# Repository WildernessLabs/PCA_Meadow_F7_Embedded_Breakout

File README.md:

# PCA_Meadow_F7_Embedded_Breakout
Printed Circuit Assembly (PCA) design of the breakout dev board for the Meadow F7 Embedded SMT Module

Designed using Kicad 5.1.6 

Import the fp-lib-table (found in the Circuit_Part_Libraries depot) to make sure your libraries work
WP_LIB is where your "Circuit_Part_Libraries\Libraried_Kicad" is located. 

Gerbers, drills and stack up are located in PCB_FAB folder
BOM is located in Assembly Folder
Pick and Place files are located in the Assembly folder

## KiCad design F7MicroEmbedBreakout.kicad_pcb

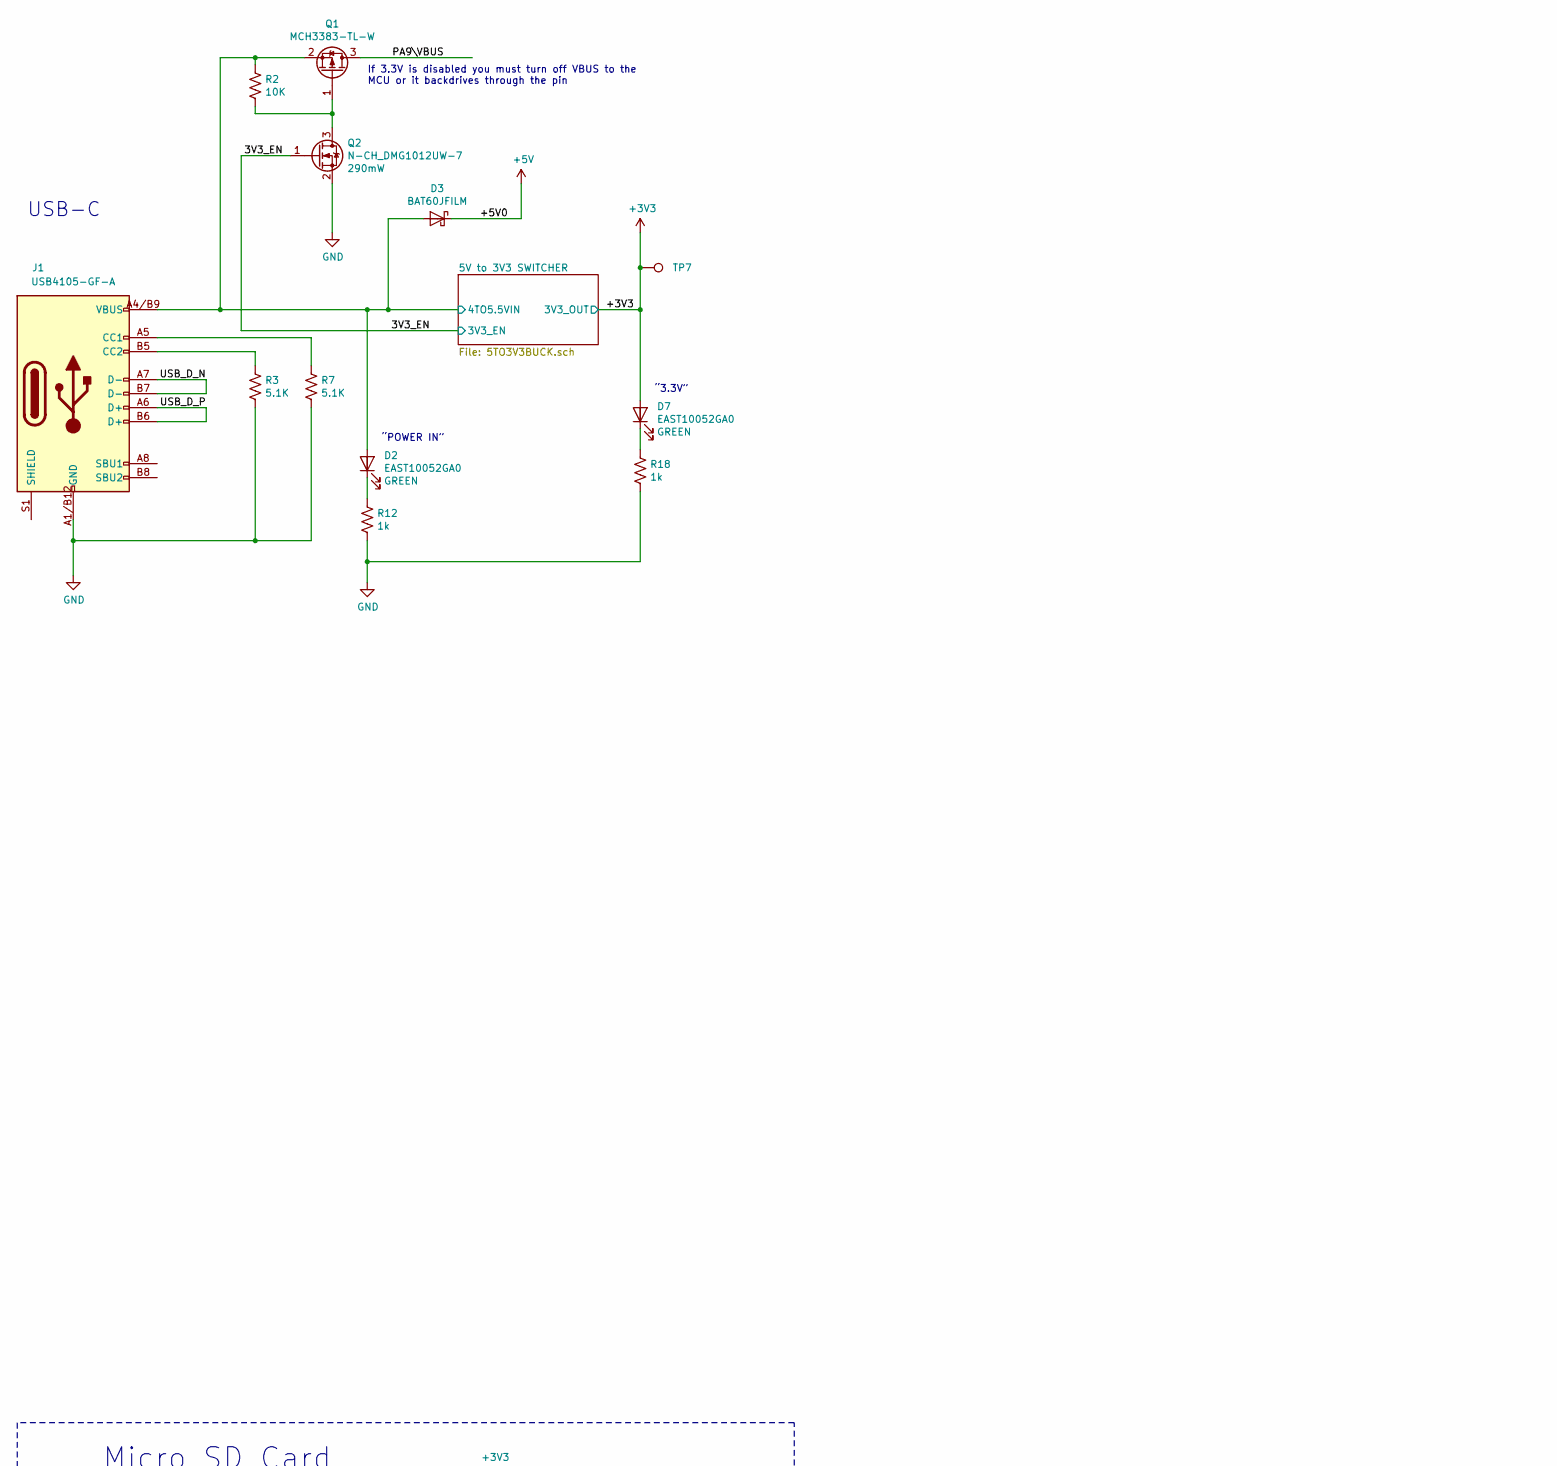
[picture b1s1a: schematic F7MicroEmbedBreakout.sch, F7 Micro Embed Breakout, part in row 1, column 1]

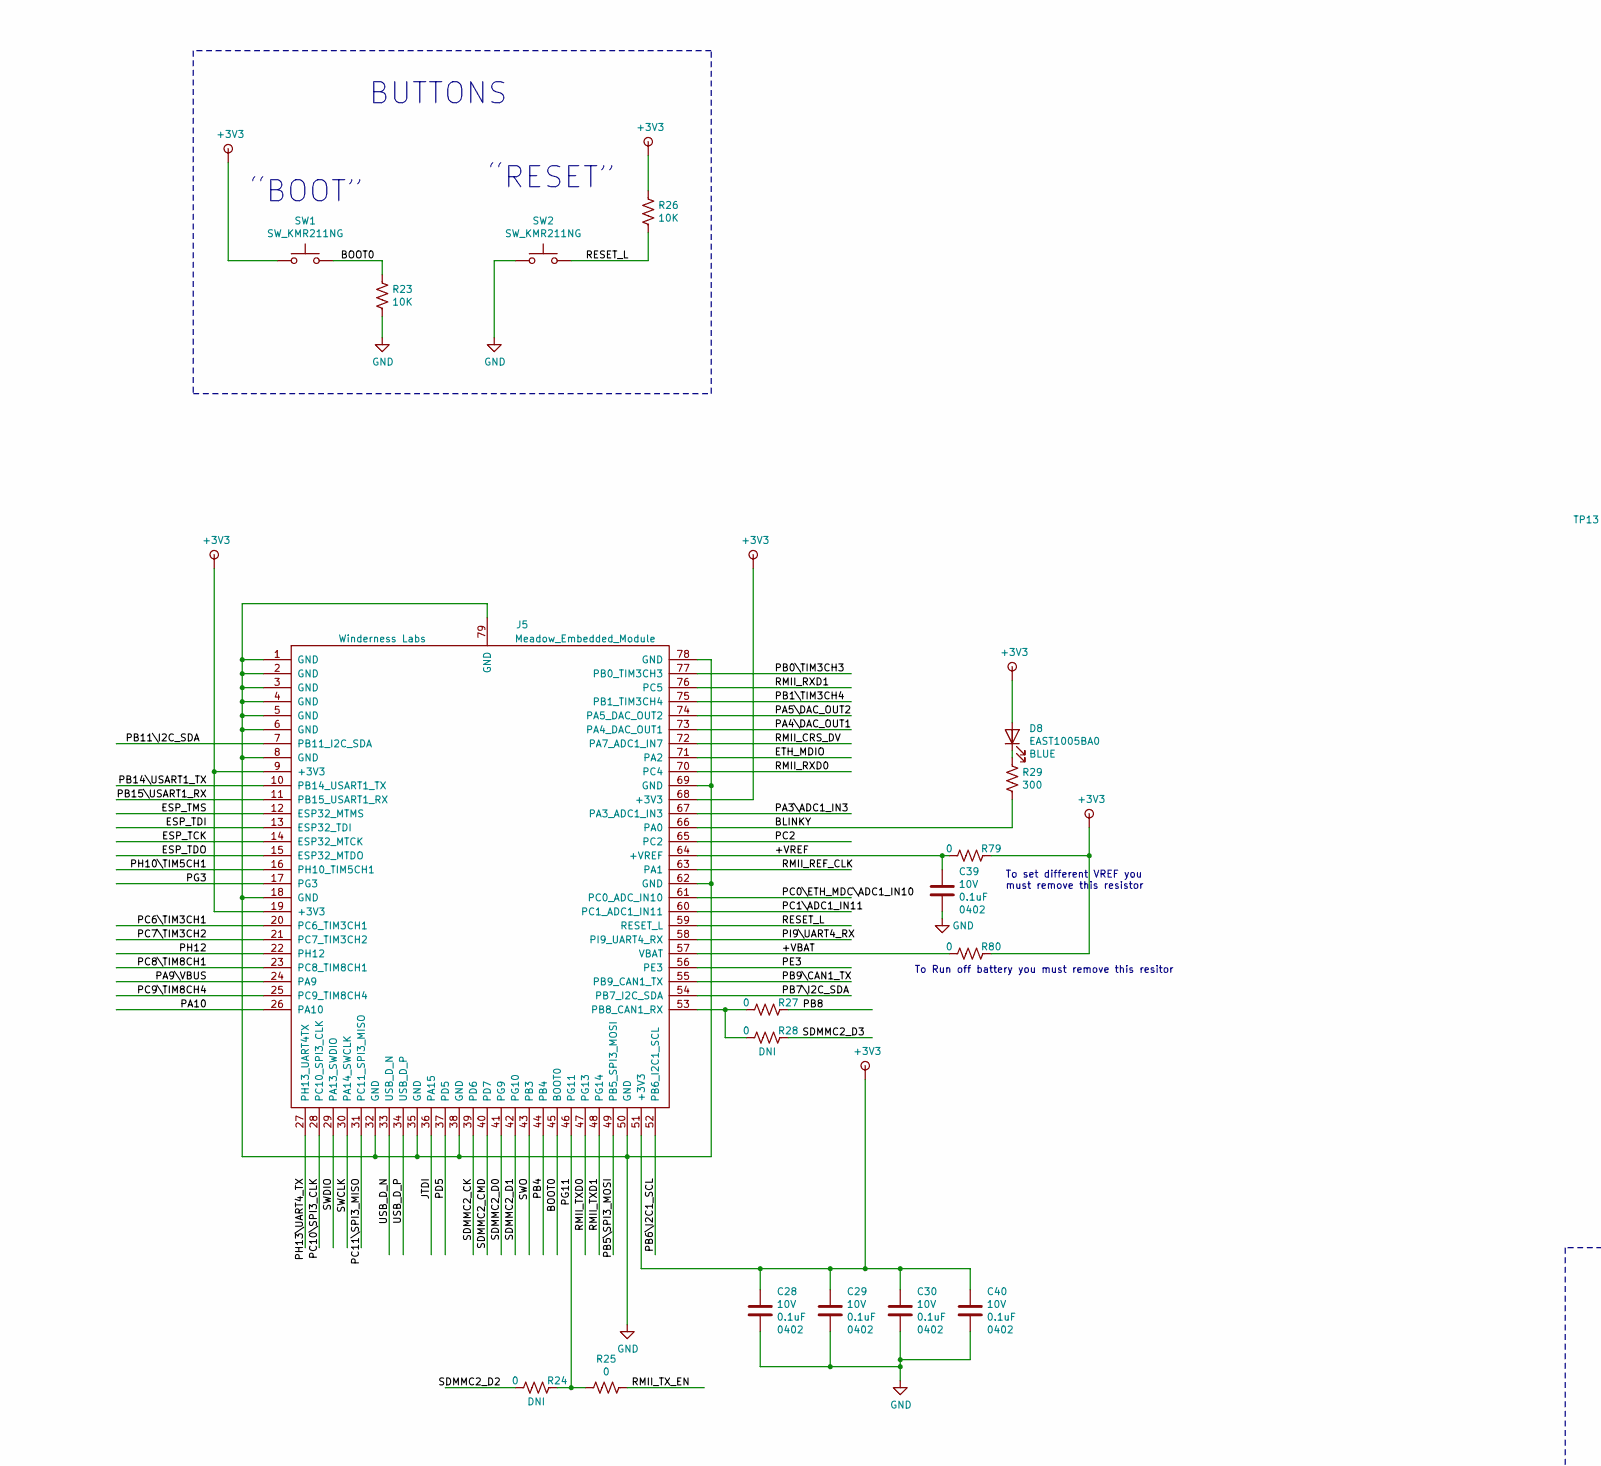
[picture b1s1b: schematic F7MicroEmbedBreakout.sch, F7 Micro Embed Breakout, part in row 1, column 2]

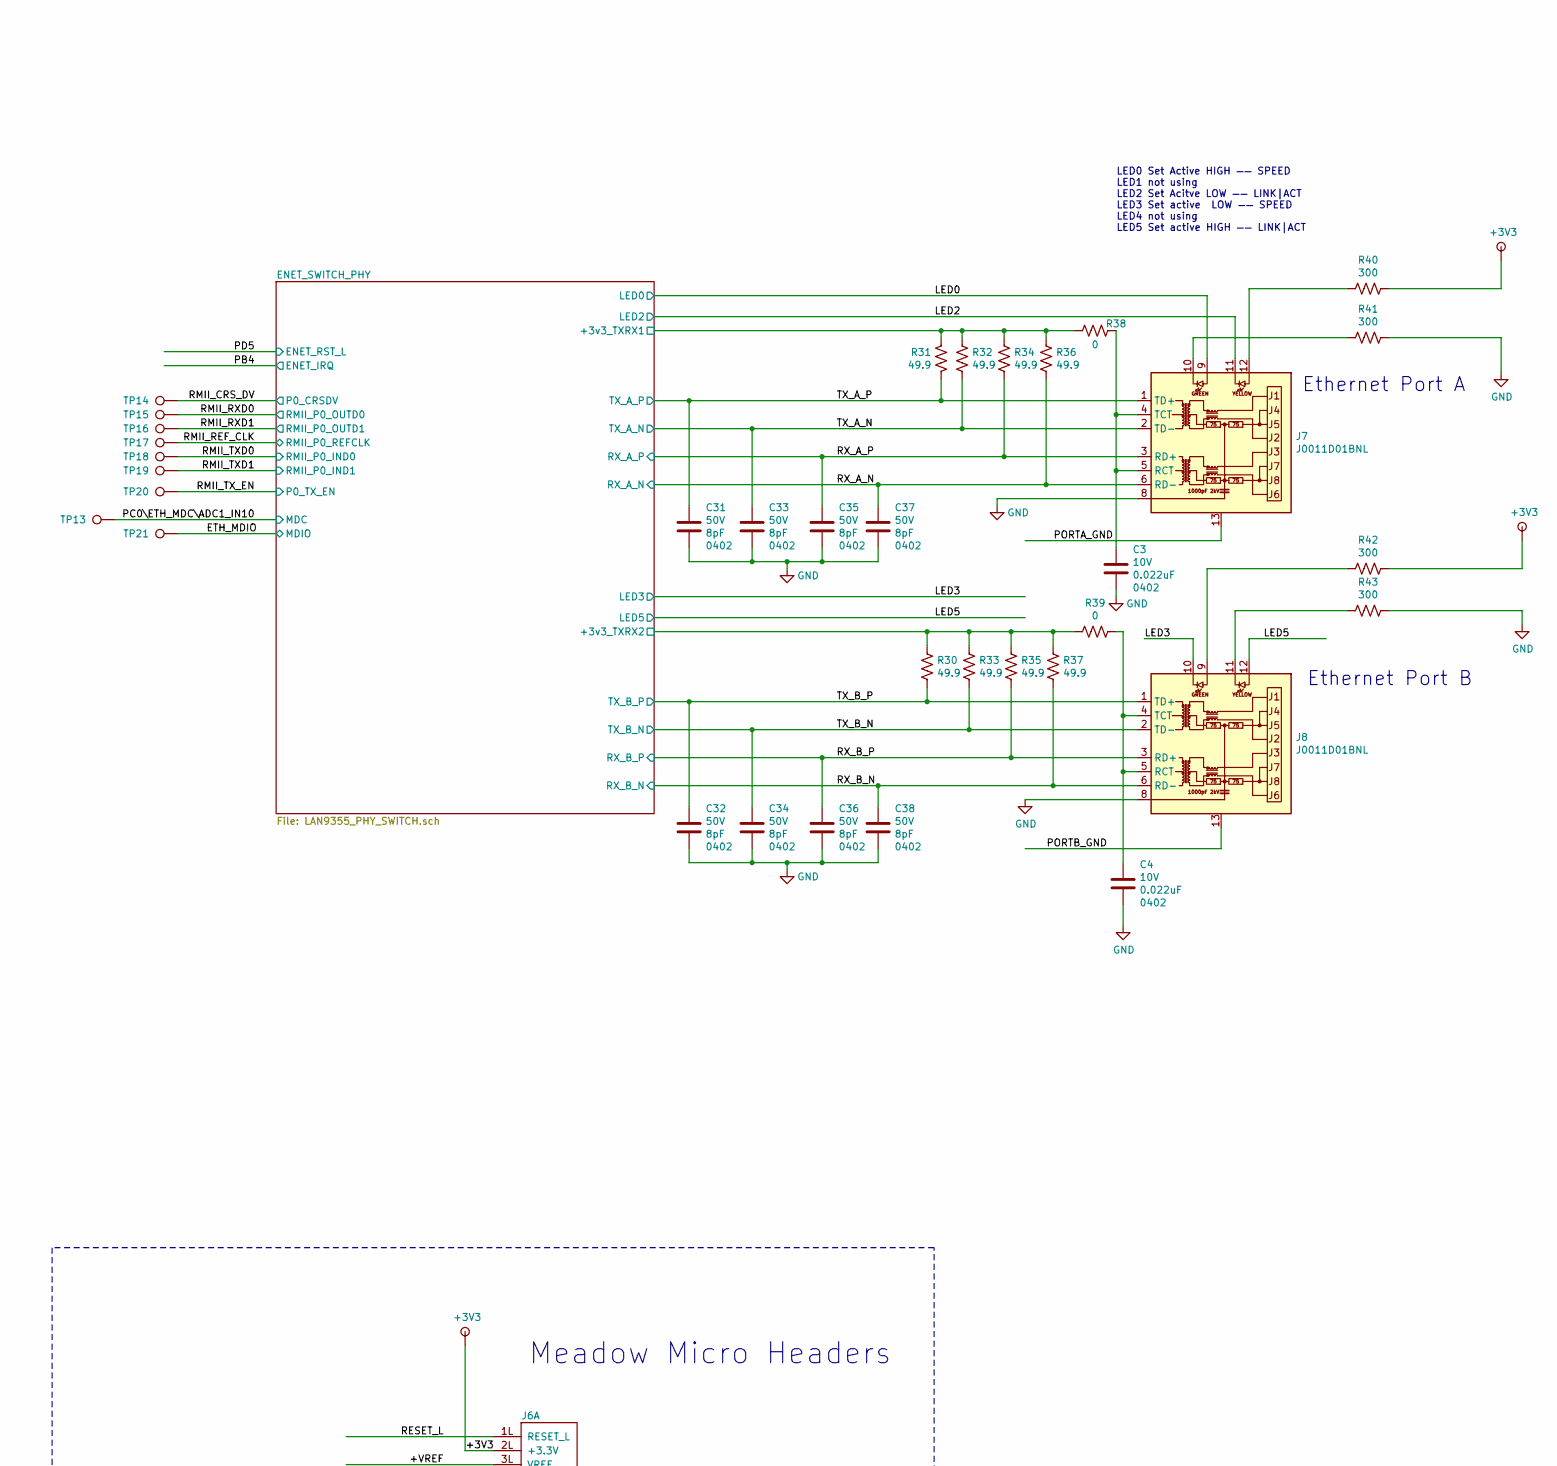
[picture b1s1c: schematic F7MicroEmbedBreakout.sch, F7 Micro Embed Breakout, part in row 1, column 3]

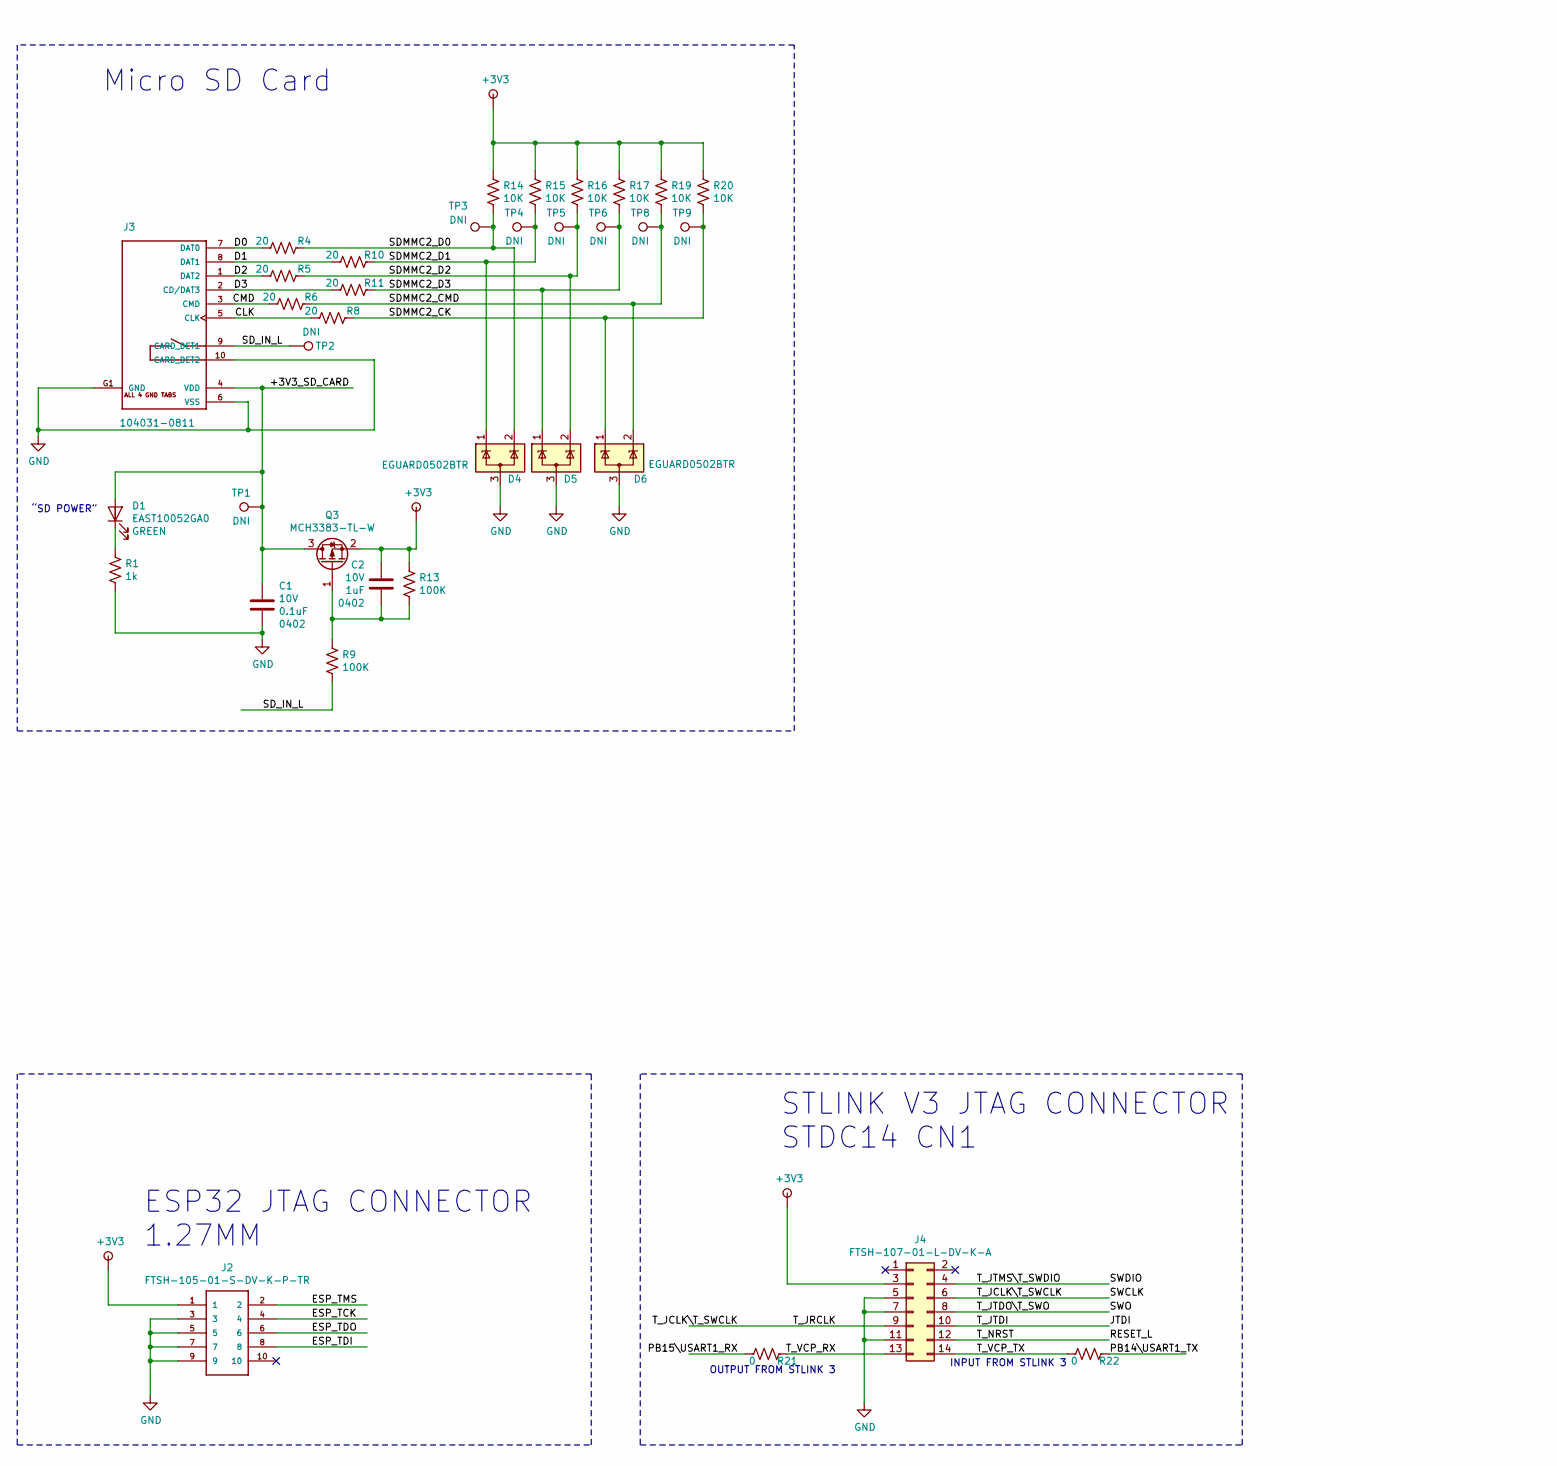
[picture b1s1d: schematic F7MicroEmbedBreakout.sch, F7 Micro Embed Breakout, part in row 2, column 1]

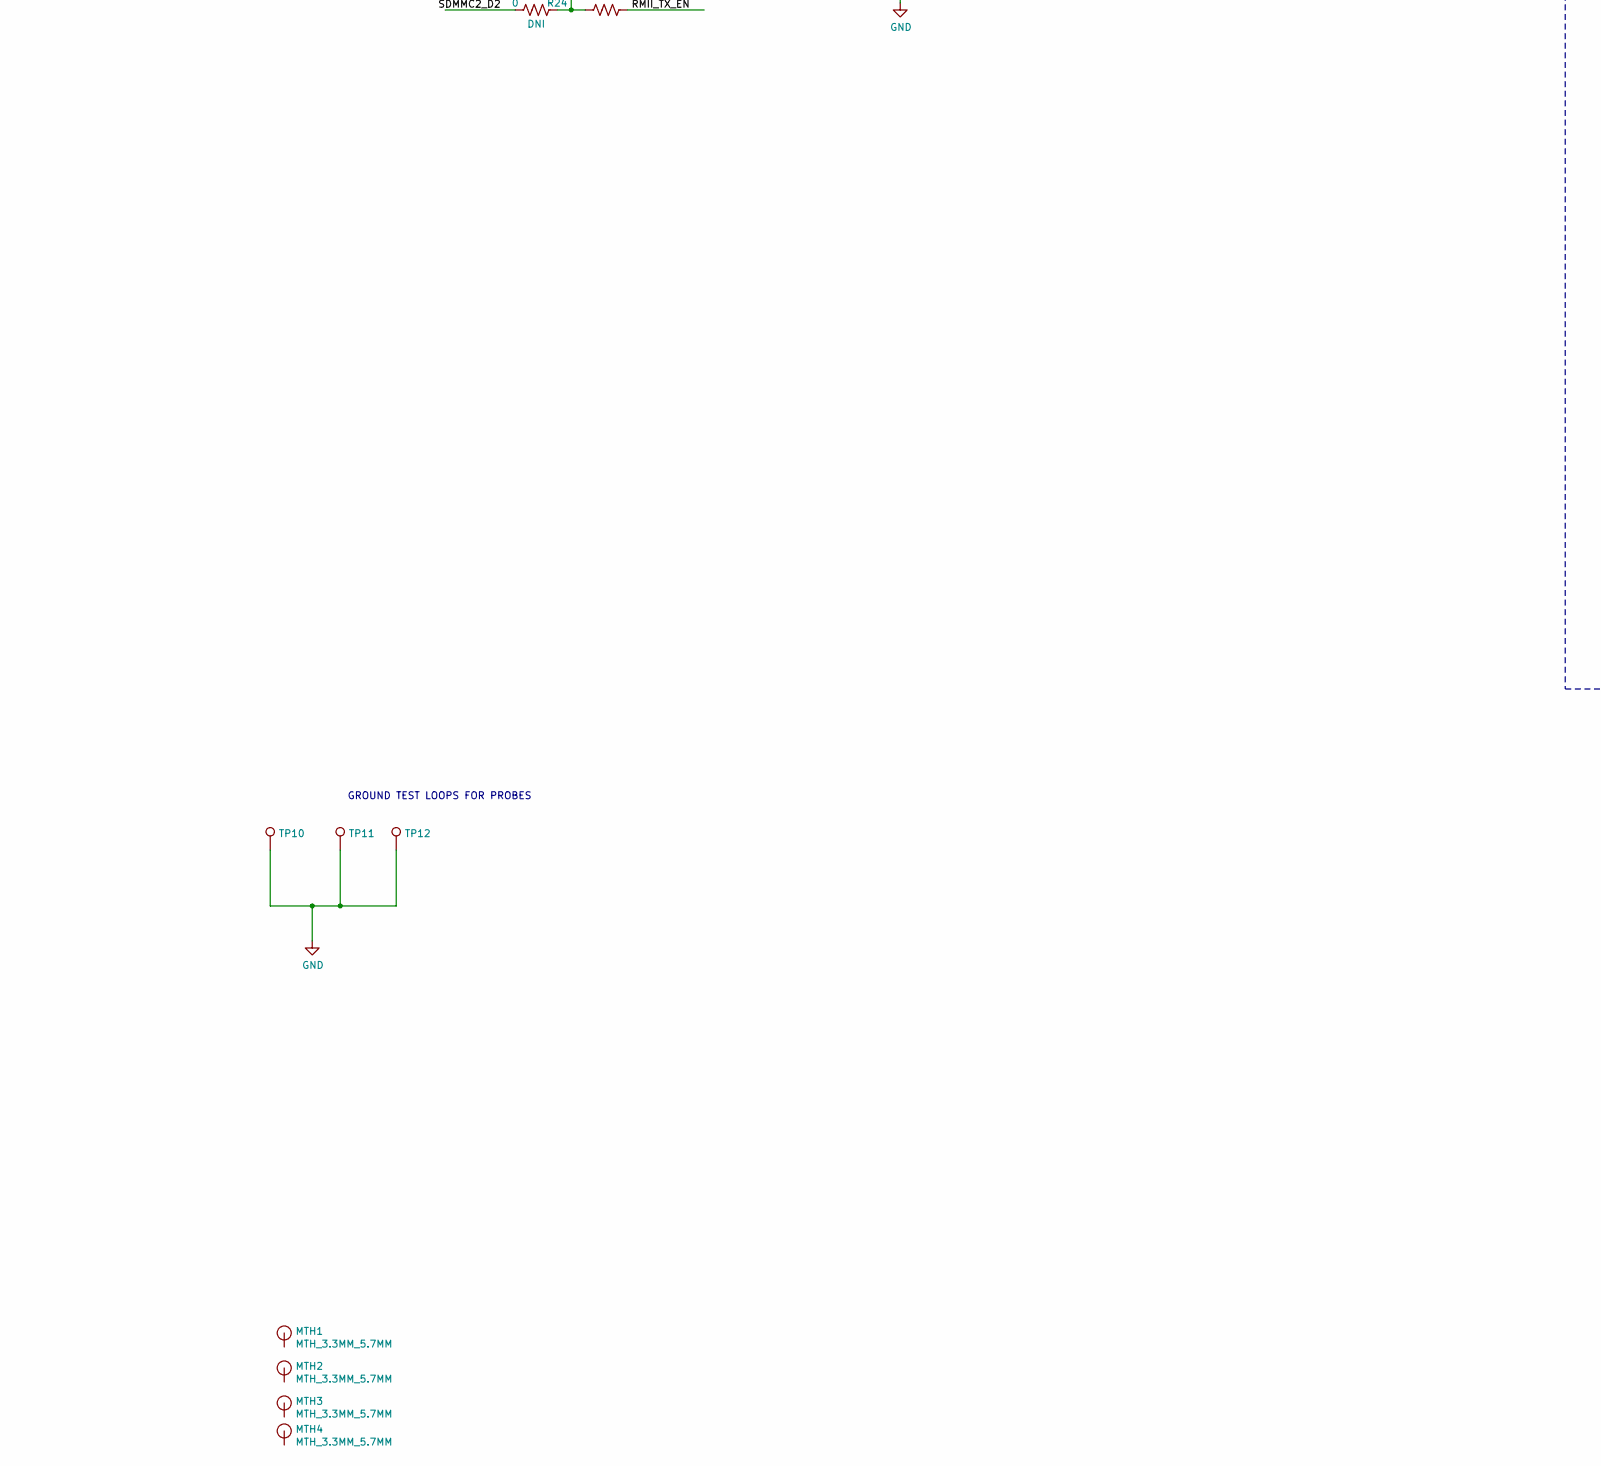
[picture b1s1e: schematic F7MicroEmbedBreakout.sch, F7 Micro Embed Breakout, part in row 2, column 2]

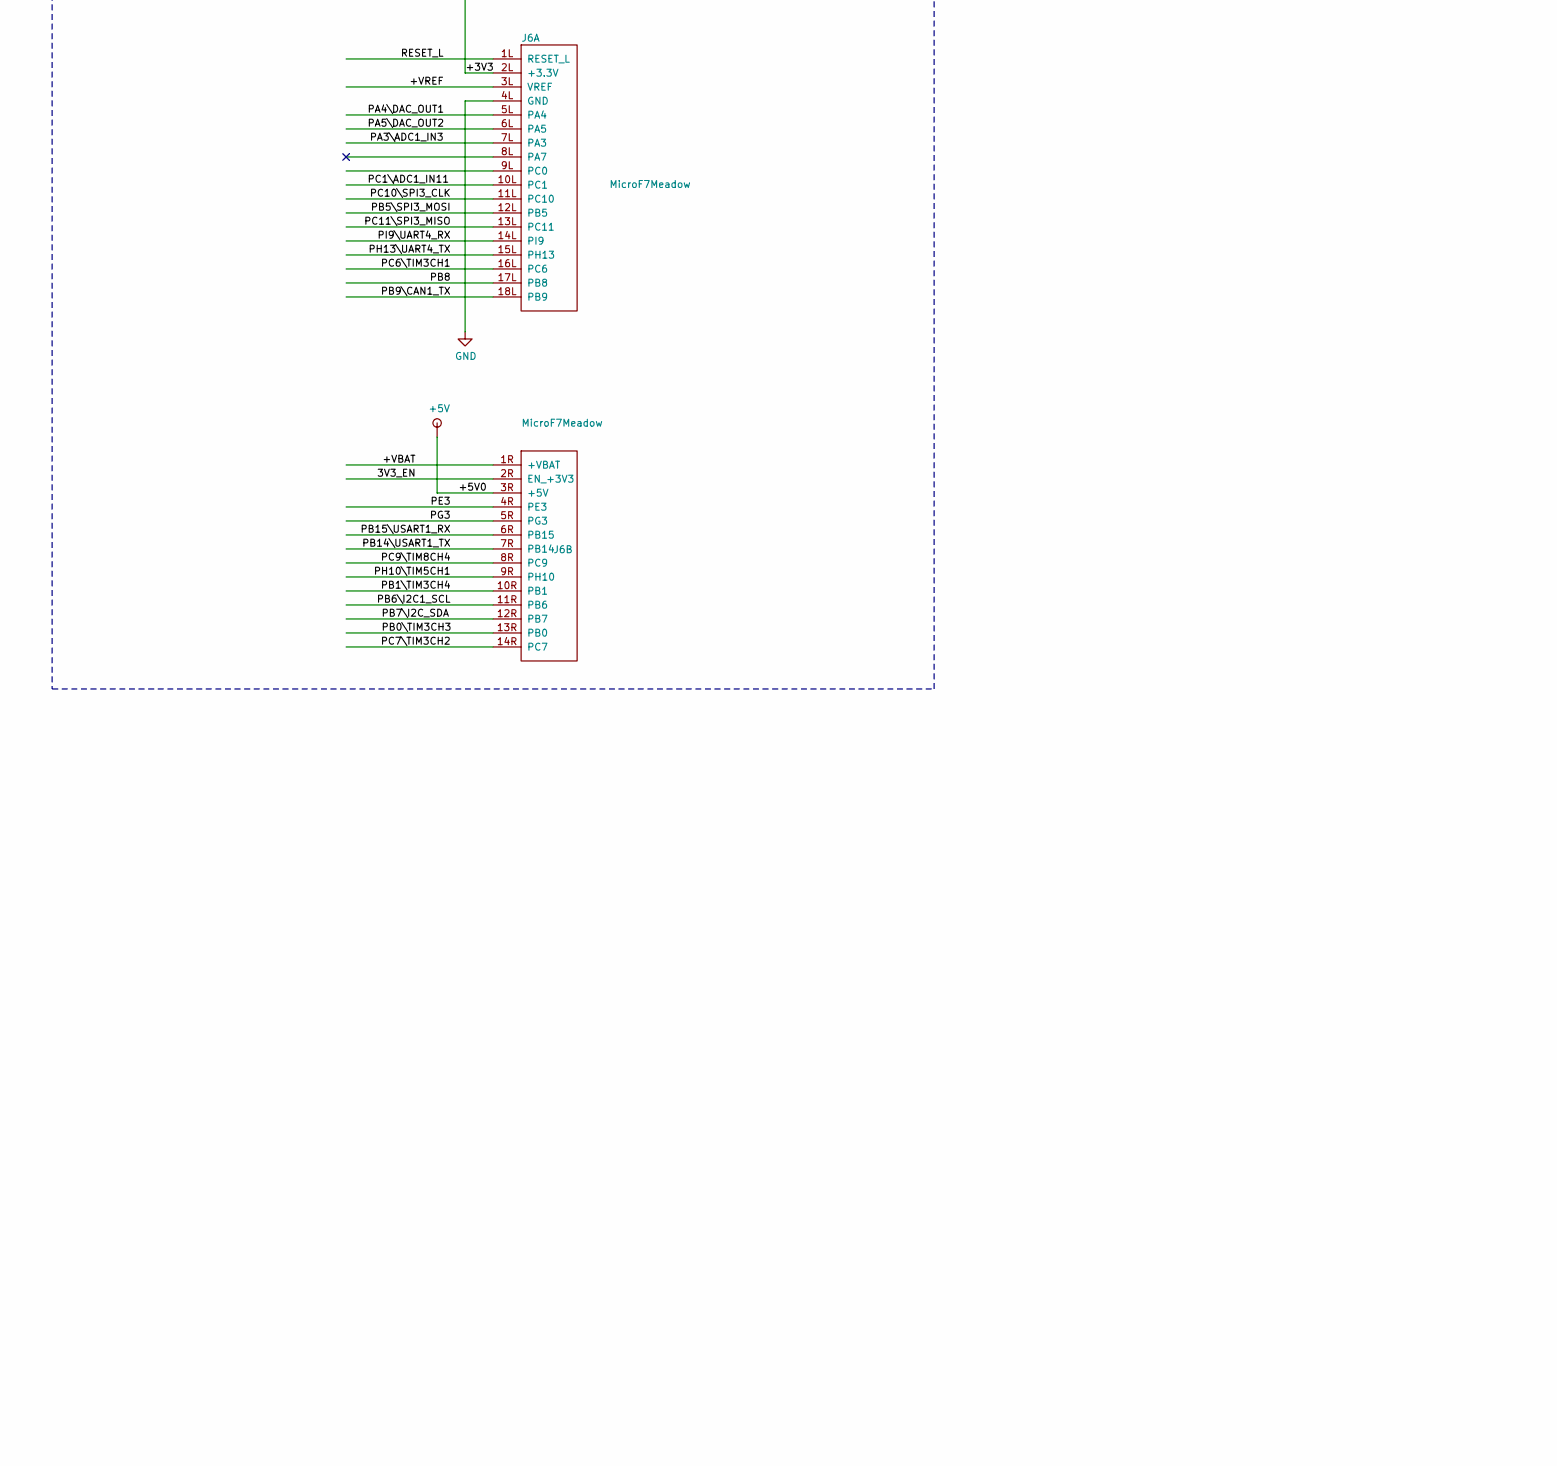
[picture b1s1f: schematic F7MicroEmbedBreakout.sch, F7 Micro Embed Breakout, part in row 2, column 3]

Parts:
C1, C28, C29, C30, C39, C40: C_0402_0.1UF_10V_X5R; C_0402_1005Metric; Voltage 10V; Tolerance 20%
C2: C_0402_1UF_10V_X5R; C_0402_1005Metric; Voltage 10V; Tolerance 20%
C3, C4: C_0402_0.022UF_50V_X5R; C_0402_1005Metric; Voltage 10V; Tolerance 10%
C31, C32, C33, C34, C35, C36, C37, C38: C_0402_8pF_50V_X5R; C_0402_1005Metric; Voltage 50V; Tolerance 0.25pF
D1, D2, D7: LED_G_EAST10052GA0; LED_0402
D3: BAT60J; D_SOD-323_HandSoldering
D4, D5, D6: EGUARD0502BTR; SOT50P160X90-3N
D8: LED_B_EAST1005BA0; LED_0402
J1: USB4105-GF-A; GCT_USB4105-GF-A
J2: SAMTEC-FTSH-105-01-X-D; SAMTEC_FTSH-105-01-X-DV-K-A
J3: 104031-0811; MOLEX_104031-0811
J4: FTSH-107-01-L-DV-K-A; SAMTEC_FTSH-107-01-L-DV-K-A
J5: Meadow_Embedded_Module; MeadowEmbeded
J6: MicroF7Meadow; MeadowF7Micro
J7, J8: J0011D01BNL; RJ45_J0011D01BNL
MTH1, MTH2, MTH3, MTH4: MTH_3.3MM_5.7MM
Q1, Q3: MCH3383-TL-W; SC-70FL
Q2: N-CH_DMG1012UW-7; SC-70FL
R1, R12, R18: R_1K_1%_0402; R_0402_1005Metric; Tolerance 1%
R2, R14, R15, R16, R17, R19, R20: R_10K_1%_0402; R_0402_1005Metric
R3, R7: R_5K1_1%_0402; R_0402_1005Metric
R4, R5, R6, R8, R10, R11: R_20_1%_0402; R_0402_1005Metric
R9, R13: R_100K_1%_0402; R_0402_1005Metric
R21, R22: R_0_1%_0402; R_0402_1005Metric
R23, R26: R_10K_1%_0402-SLJ_Resistor_0402; R_0402_1005Metric
R24, R25, R27, R28, R38, R39, R79, R80: R_0R_1%_0603; R_0402_1005Metric; Tolerance 1%
R29, R40, R41, R42, R43: R_300_1%_0402; R_0402_1005Metric
R30, R31, R32, R33, R34, R35, R36, R37: R_49R9_1%_0402; R_0402_1005Metric; Tolerance 1%
SW1, SW2: SW_KMR211NG; KMR211NG
TP1, TP2, TP3, TP4, TP5, TP6, TP7, TP8, TP9, TP13, TP14, TP15, TP16, TP17, TP18, TP19, TP20, TP21: TestPoint_SMT_25mil; PAD_RD_0.63
TP10, TP11, TP12: TestPoint_SMT_loop_1X1.8MM; TP_S2761-46R

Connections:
+3V3: C2.2, C28.1, C29.1, C30.1, C40.1, D7.1 (A), D8.1 (A), J2.1, J4.3, J5.9 (+3V3), J5.19 (+3V3), J5.51 (+3V3), J5.68 (+3V3), J6.2L (+3.3V), Q3.2 (S), R13.1, R14.1, R15.1, R16.1, R17.1, R19.1, R20.1, R26.1, R40.1, R42.1, R79.1, R80.1, SW1.1, SW1.4, TP7.1; also elsewhere on the board
+5V: D3.1 (K), J6.3R (+5V)
/3V3_EN: J6.2R (EN_+3V3), Q2.1 (G); also elsewhere on the board
/5V to 3V3 SWITCHER/4TO5.5VIN: D2.1 (A), D3.2 (A), J1.A4/B9 (VBUS), J1.B4/A9 (VBUS), Q1.2 (S), R2.1; also elsewhere on the board
/+3V3_SD_CARD: C1.1, D1.1 (A), J3.4 (VDD), Q3.3 (D), TP1.1
/+VBAT: J5.57 (VBAT), J6.1R (+VBAT), R80.2
/+VREF: C39.1, J5.64 (+VREF), J6.3L (VREF), R79.2
/BLINKY: J5.66 (PA0), R29.2
/BOOT0: J5.45 (BOOT0), R23.1, SW1.2, SW1.3
/CLK: J3.5 (CLK), R8.2
/CMD: J3.3 (CMD), R6.2
/D0: J3.7 (DAT0), R4.2
/D1: J3.8 (DAT1), R10.2
/D2: J3.1 (DAT2), R5.2
/D3: J3.2 (CD/DAT3), R11.2
/ENET_SWITCH_PHY/+3v3_TXRX1: R31.2, R32.1, R34.1, R36.1, R38.2; also elsewhere on the board
/ENET_SWITCH_PHY/+3v3_TXRX2: R30.1, R33.1, R35.1, R37.1, R39.2; also elsewhere on the board
/ESP_TCK: J2.4, J5.14 (ESP32_MTCK)
/ESP_TDI: J2.8, J5.13 (ESP32_TDI)
/ESP_TDO: J2.6, J5.15 (ESP32_MTDO)
/ESP_TMS: J2.2, J5.12 (ESP32_MTMS)
/ETH_MDIO: J5.71 (PA2), TP21.1; also elsewhere on the board
/JTDI: J4.10, J5.36 (PA15)
/LED0: J7.9; also elsewhere on the board
/LED2: J7.11; also elsewhere on the board
/LED3: J8.10; also elsewhere on the board
/LED5: J8.12; also elsewhere on the board
/PA3\ADC1_IN3: J5.67 (PA3_ADC1_IN3), J6.7L (PA3)
/PA4\DAC_OUT1: J5.73 (PA4_DAC_OUT1), J6.5L (PA4)
/PA5\DAC_OUT2: J5.74 (PA5_DAC_OUT2), J6.6L (PA5)
/PA9\VBUS: J5.24 (PA9), Q1.3 (D)
/PA10: J5.26 (PA10)
/PB0\TIM3CH3: J5.77 (PB0_TIM3CH3), J6.13R (PB0)
/PB1\TIM3CH4: J5.75 (PB1_TIM3CH4), J6.10R (PB1)
/PB4: J5.44 (PB4); also elsewhere on the board
/PB5\SPI3_MOSI: J5.49 (PB5_SPI3_MOSI), J6.12L (PB5)
/PB6\I2C1_SCL: J5.52 (PB6_I2C1_SCL), J6.11R (PB6)
/PB7\I2C_SDA: J5.54 (PB7_I2C_SDA), J6.12R (PB7)
/PB8: J6.17L (PB8), R27.1
/PB9\CAN1_TX: J5.55 (PB9_CAN1_TX), J6.18L (PB9)
/PB11\I2C_SDA: J5.7 (PB11_I2C_SDA)
/PB14\USART1_TX: J5.10 (PB14_USART1_TX), J6.7R (PB14), R22.1
/PB15\USART1_RX: J5.11 (PB15_USART1_RX), J6.6R (PB15), R21.2
/PC0\ETH_MDC\ADC1_IN10: J5.61 (PC0_ADC_IN10), TP13.1; also elsewhere on the board
/PC1\ADC1_IN11: J5.60 (PC1_ADC1_IN11), J6.10L (PC1)
/PC2: J5.65 (PC2)
/PC6\TIM3CH1: J5.20 (PC6_TIM3CH1), J6.16L (PC6)
/PC7\TIM3CH2: J5.21 (PC7_TIM3CH2), J6.14R (PC7)
/PC8\TIM8CH1: J5.23 (PC8_TIM8CH1)
/PC9\TIM8CH4: J5.25 (PC9_TIM8CH4), J6.8R (PC9)
/PC10\SPI3_CLK: J5.28 (PC10_SPI3_CLK), J6.11L (PC10)
/PC11\SPI3_MISO: J5.31 (PC11_SPI3_MISO), J6.13L (PC11)
/PD5: J5.37 (PD5); also elsewhere on the board
/PE3: J5.56 (PE3), J6.4R (PE3)
/PG3: J5.17 (PG3), J6.5R (PG3)
/PG11: J5.46 (PG11), R24.1, R25.2
/PH10\TIM5CH1: J5.16 (PH10_TIM5CH1), J6.9R (PH10)
/PH12: J5.22 (PH12)
/PH13\UART4_TX: J5.27 (PH13_UART4TX), J6.15L (PH13)
/PI9\UART4_RX: J5.58 (PI9_UART4_RX), J6.14L (PI9)
/PORTA_GND: J7.13
/PORTB_GND: J8.13
/RESET_L: J4.12, J5.59 (RESET_L), J6.1L (RESET_L), R26.2, SW2.2, SW2.3
/RMII_CRS_DV: J5.72 (PA7_ADC1_IN7), TP14.1; also elsewhere on the board
/RMII_REF_CLK: J5.63 (PA1), TP17.1; also elsewhere on the board
/RMII_RXD0: J5.70 (PC4), TP15.1; also elsewhere on the board
/RMII_RXD1: J5.76 (PC5), TP16.1; also elsewhere on the board
/RMII_TXD0: J5.47 (PG13), TP18.1; also elsewhere on the board
/RMII_TXD1: J5.48 (PG14), TP19.1; also elsewhere on the board
/RMII_TX_EN: R25.1, TP20.1; also elsewhere on the board
/RX_A_N: C37.1, J7.6 (RD-), R36.2; also elsewhere on the board
/RX_A_P: C35.1, J7.3 (RD+), R34.2; also elsewhere on the board
/RX_B_N: C38.1, J8.6 (RD-), R37.2; also elsewhere on the board
/RX_B_P: C36.1, J8.3 (RD+), R35.2; also elsewhere on the board
/SDMMC2_CK: D6.1 (K), J5.39 (PD6), R8.1, R20.2, TP9.1
/SDMMC2_CMD: D6.2 (K), J5.40 (PD7), R6.1, R19.2, TP8.1
/SDMMC2_D0: D4.2 (K), J5.41 (PG9), R4.1, R14.2, TP3.1
/SDMMC2_D1: D4.1 (K), J5.42 (PG10), R10.1, R15.2, TP4.1
/SDMMC2_D2: D5.2 (K), R5.1, R16.2, R24.2, TP5.1
/SDMMC2_D3: D5.1 (K), R11.1, R17.2, R28.1, TP6.1
/SD_IN_L: J3.9 (CARD_DET1), R9.2, TP2.1
/SWCLK: J4.6, J4.9, J5.30 (PA14_SWCLK)
/SWDIO: J4.4, J5.29 (PA13_SWDIO)
/SWO: J4.8, J5.43 (PB3)
/TX_A_N: C33.1, J7.2 (TD-), R32.2; also elsewhere on the board
/TX_A_P: C31.1, J7.1 (TD+), R31.1; also elsewhere on the board
/TX_B_N: C34.1, J8.2 (TD-), R33.2; also elsewhere on the board
/TX_B_P: C32.1, J8.1 (TD+), R30.2; also elsewhere on the board
/T_VCP_RX: J4.13, R21.1
/T_VCP_TX: J4.14, R22.2
/USB_D_N: J1.A7 (D-), J1.B7 (D-), J5.33 (USB_D_N)
/USB_D_P: J1.A6 (D+), J1.B6 (D+), J5.34 (USB_D_P)
GND: C1.2, C3.2, C4.2, C28.2, C29.2, C30.2, C31.2, C32.2, C33.2, C34.2, C35.2, C36.2, C37.2, C38.2, C39.2, C40.2, D4.3 (A), D5.3 (A), D6.3 (A), J1.A1/B12 (GND), J1.B1/A12 (GND), J2.3, J2.5, J2.7, J2.9, J3.6 (VSS), J3.10 (CARD_DET2), J3.G1 (GND), J3.G2 (GND), J3.G3 (GND), J3.G4 (GND), J4.5, J4.7, J4.11, J5.1 (GND), J5.2 (GND), J5.3 (GND), J5.4 (GND), J5.5 (GND), J5.6 (GND), J5.8 (GND), J5.18 (GND), J5.32 (GND), J5.35 (GND), J5.38 (GND), J5.50 (GND), J5.62 (GND), J5.69 (GND), J5.78 (GND), J5.79 (GND), J6.4L (GND), J7.8, J8.8, Q2.2 (S), R1.2, R3.2, R7.2, R12.2, R18.2, R23.2, R41.1, R43.1, SW2.1, SW2.4, TP10.1, TP11.1, TP12.1; also elsewhere on the board
unnamed: C2.1, Q3.1 (G), R9.1, R13.2
unnamed: C3.1, J7.4 (TCT), J7.5 (RCT), R38.1
unnamed: C4.1, J8.4 (TCT), J8.5 (RCT), R39.1
unnamed: D1.2 (K), R1.1
unnamed: D2.2 (K), R12.1
unnamed: D7.2 (K), R18.1
unnamed: D8.2 (K), R29.1
unnamed: J1.A5 (CC1), R7.1
unnamed: J1.B5 (CC2), R3.1
unnamed: J5.53 (PB8_CAN1_RX), R27.2, R28.2
unnamed: J7.10, R41.2
unnamed: J7.12, R40.2
unnamed: J8.9, R42.2
unnamed: J8.11, R43.2
unnamed: Q1.1 (G), Q2.3 (D), R2.2

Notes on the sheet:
Micro SD Card
USB-C
Ethernet Port A
Ethernet Port B
OUTPUT FROM STLINK 3
INPUT FROM STLINK 3
STLINK V3 JTAG CONNECTOR STDC14 CN1
ESP32 JTAG CONNECTOR 1.27MM
Meadow Micro Headers
“BOOT”
“RESET”
BUTTONS
“SD POWER”
“POWER IN”
“3.3V”
If 3.3V is disabled you must turn off VBUS to the MCU or it backdrives through the pin
LED0 Set Active HIGH —— SPEED LED1 not using LED2 Set Acitve LOW —— LINK|ACT LED3 Set active LOW —— SPEED LED4 not using LED5 Set active HIGH —— LINK|ACT
GROUND TEST LOOPS FOR PROBES
To Run off battery you must remove this resitor
To set different VREF you must remove this resistor

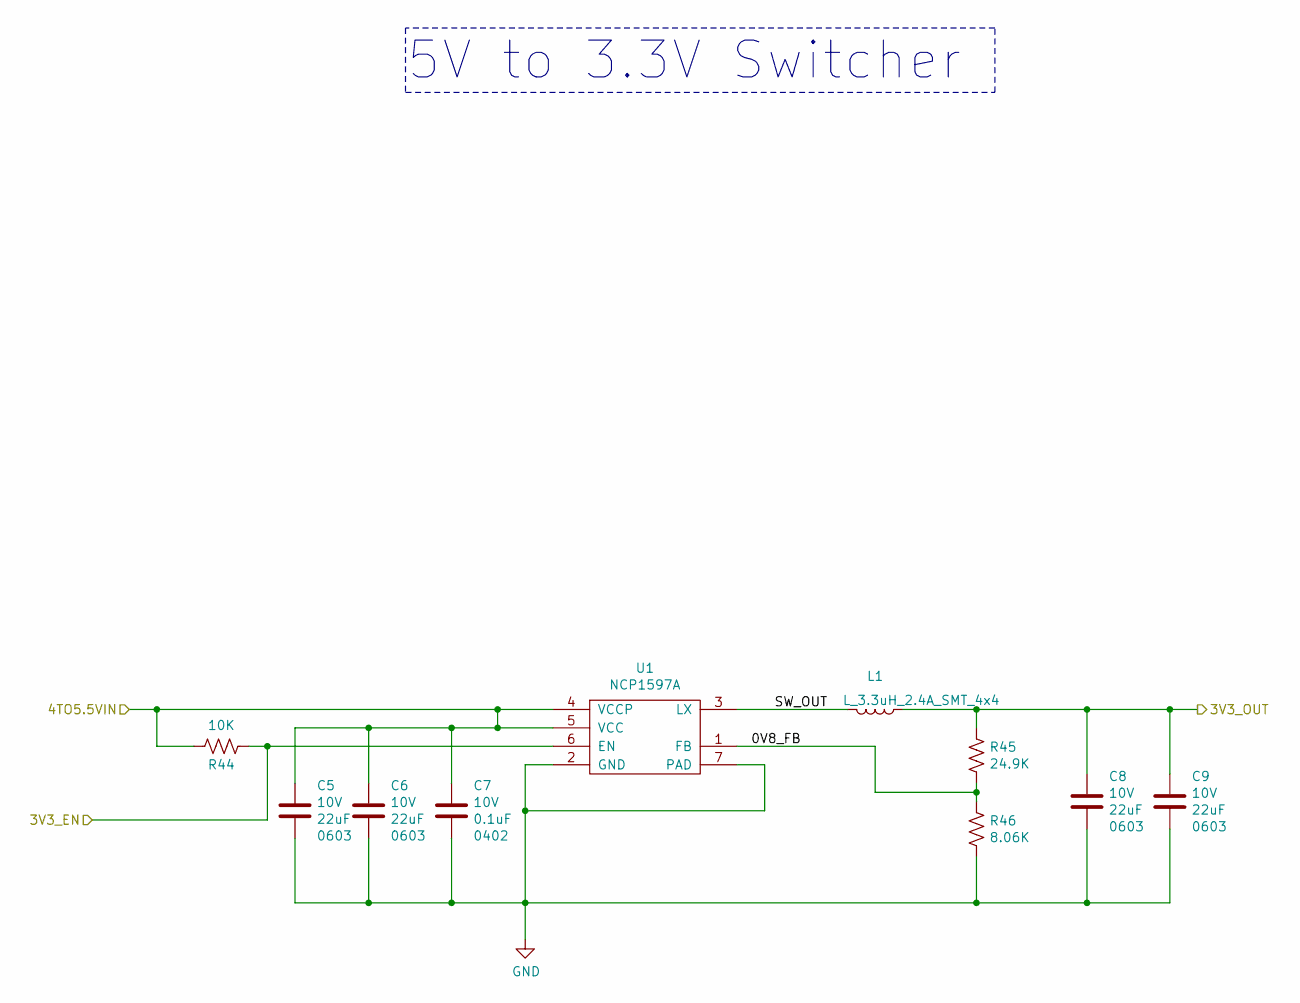
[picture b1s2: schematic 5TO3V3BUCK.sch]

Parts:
C5, C6, C8, C9: C_0603_22UF_10V_X5R; C_0603_1608Metric; Voltage 10V; Tolerance 20%
C7: C_0402_0.1UF_10V_X5R; C_0402_1005Metric; Voltage 10V; Tolerance 20%
L1: L_3.3uH_2.4A_SMT_4x4; Inductor_Abracon_ASPI-4030
R44: R_10K_1%_0402; R_0402_1005Metric
R45: R_24K9_1%_0402; R_0402_1005Metric
R46: R_8K06_1%_0402; R_0402_1005Metric
U1: NCP1597A; DFN-6-1EP_3x3mm_Pitch0.95mm

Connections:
+3V3: C8.1, C9.1, L1.1, R45.1; also elsewhere on the board
/3V3_EN: R44.1, U1.6 (EN); also elsewhere on the board
/5V to 3V3 SWITCHER/0V8_FB: R45.2, R46.1, U1.1 (FB)
/5V to 3V3 SWITCHER/4TO5.5VIN: C5.1, C6.1, C7.1, R44.2, U1.4 (VCCP), U1.5 (VCC); also elsewhere on the board
/5V to 3V3 SWITCHER/SW_OUT: L1.2, U1.3 (LX)
GND: C5.2, C6.2, C7.2, C8.2, C9.2, R46.2, U1.2 (GND), U1.7 (PAD); also elsewhere on the board

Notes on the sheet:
5V to 3.3V Switcher
